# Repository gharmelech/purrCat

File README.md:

# **purrCat**

This is a novelty PCB Art of a purring cat.

Feel free to use this project or parts of it at will, but please give credit when doing so.

While this is an open source project, I am selling kits and assembled units for 10 and 15 USD respectivly.  
Please consider supporting us by [ordering here](https://forms.gle/wS7aRQJ3xb9KGsVB8).

## **Art**
The art was made by Taly Reznik - [@trollworks](https://www.instagram.com/trollworks/?fbclid=IwAR2XS3pt9mpKQIKOb-wqeVHk0iGZXp5bulvpvjSy-UH8qeWS0hPnVhlgy5U)  
Go check out her awesome work!

## **Hardware Description**
The project is based on TI's msp430fr2111 MCU. The current software could fit in (and easily compiled for) msp430fr2110 and could probably be further optimized to fit msp430fr2100, but going with the 2111 model leaves a lot of room for future expansion with just a small price difference.  

Purring is achived with a round radial vibration motor, which is low-side controlled with an nmos transistor.  
In addition, the eyes light up using reverse-mounted LEDs (might be worthwhile to change it to a side view LED in the future).  

Petting is detected using capacitive touch.  
There are 4 touch pads on the PCB, but only 1 is in use in the current FW.

### **Some FW details**

#### **Picky Cat!**
I wanted to make the cat as realistic as possible, so it only likes petting between 0.5 and 2Hz.  
(*Since I'm not doing swipe detection, it would also work with tapping. I might change it in a future version*)  
This is achived using a 2s sample buffer with 125ms slots. if the pad is touched for more than 3 slots in a row, the buffer zeroes.  
Furthermore, purring only starts after at least 1s of petting.

#### **Realistic Purring**
I have programmed a simple PWM function to make the vibration feel like real purring.  
It has dynamic change to the duty cycle, this creates the subtle ramp-up and ramp-down typical of a cat's purring.  
I tried a sinusoidal PWM function, but it didn't have the right feel to it.

#### **Programming and flashing**
The MCU is programmed using Code Composer Studio IDE.  
For software flashing I use a TI dev board LAUNCHPAD MSP-EXP430FR2433, which is the lowest cost programmer option available, though I assume you could make a flashing device out of an arduino.  
I left 3x2mm pitch pads for programming right near the MCU.  
They are arranged (from top to bottom) GND-SBWTCK-SBWTDIO, an additional connection to VCC is required and could be obtained from the battery clip.

### **Power Consumption**
The FW used to feature a distinct power saving mode, but changing the wait timer to RTC with VLO clock source randered that mode as unnedded.  
It is still available in code using a #define flag.

In the current configuration, sampling consumes about 2 micro Ampere - around 60uW at nominal 3V.  
When Purring, i.e. when the motor and the LEDs are enabled, the current consumption is about 22mA - 66mW at nonminal 3V.

The final design uses a cr2032 lithium cell which are rated at about 240mAh.  
While theoretical battery life should have been roughly 8 hours of purring or about 6 years of idle,  
The 240mAh rating is given at much lower current draw than that of the active purring.  
At 20mA, most cr2032 have a capacity of a mere 10-15mAh, giving only about 30 minutes of active purring.

I don't have a good explantion for it, but idle time also seems to substencialy lower than the theoretical - getting to around one week.

Note that this is not linear and even a small reduction in current draw while purring would result in longer operation time.  
Sadly, I was'nt able to find a way to reduce to consumption enough.

#### **LiPo mod**
Giving the poor battery life, I designed a small PCB holding an LDO and a charge connector for a LiPo, to be soldered instead of the battery clip.
The thought of using a LiPo crossed my mind several times, but I deemed it unvaiabel because of cost and required PCB space for a charge controller.
Finally, I had the realization to use a generic LiPo charger externaly (which could be obtained from AliExpress for very cheap) instead of making it onboard.
I did changed the current select resistor on the charger such that the max charge current will be 100 mA - suitable for the tiny LiPo I use.

I decided to use a 501015 60mAh battery.
Because these are rated at 1C, we get a runtime much closer to the theoretical value - about 1.5 hours of purring!
I have used a sub-optimal LDO with 30 uA quiescent current, which becomes the dominant current draw during idle.
I calculated arround 40 days of idle time, but have not ran this long time test yet.

### **Parts List**
- MCU: msp430fr2111
- LED: 2x 0805 LED (reverse mounted, color of your choice)
- Capacitors: 2x0805 10uF MLCC (1 for the MCU and 1 for the Motor), 1x0603 100nF MLCC (for the MCU)
- Resistors: 3x0603 1k Ohm (current limiting for the transistor and the LEDs), 1x0603 100k Ohm (pulldown for the transistor, could be omitted as the driver pin is push-pull)
- Diode: 1x0603 schottky diode (I used Kyocera AVX SD0603S040S0R2)
- Transistor: 1xSOT3 NMOS Transistor (I used Nexperia NXV55UNR)
- Battery clip: 1x Keystone 3034 (cr2032 battery holder), note that not all battery holders can fit in the PCBs footprint)
- Vibration motor: 1x 10mm round radial vibration motor(or smaller), note that there are no pads for soldering it. one lead should be connected to vcc(I used the cap for it) and the other to the transistor drain pin (I made a bigger pad to accomodate this).

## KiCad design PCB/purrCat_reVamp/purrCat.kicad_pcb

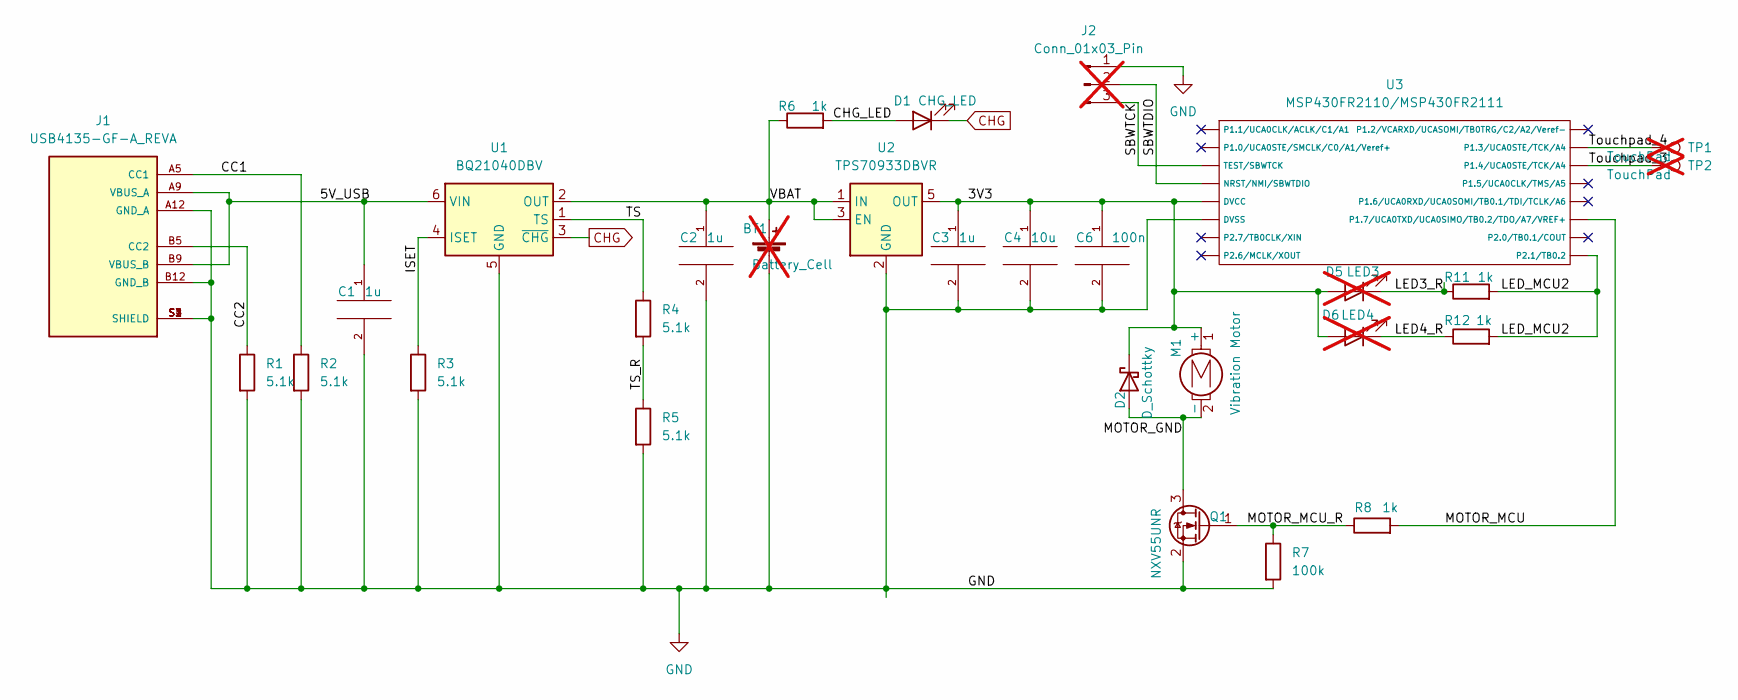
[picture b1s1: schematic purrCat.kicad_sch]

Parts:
BT1: Battery_Cell; bat_solder_pads; not fitted
C1, C2, C3: 1u; C_0603_1608Metric
C4: 10u; C_0805_2012Metric
C6: 100n; C_0402_1005Metric
D1: CHG_LED; LED_0603_1608Metric
D2: D_Schottky; D_0603_1608Metric
D5: LED3; LED_1206_3216Metric_shinethrough; not fitted
D6: LED4; LED_1206_3216Metric_shinethrough; not fitted
J1: USB4135-GF-A_REVA; USB_C_Receptacle_GCT_USB4135-GF-A_6P_TopMnt_Horizontal; PARTREV A
J2: Conn_01x03_Pin; PinHeader_1x03_programmer; not fitted
M1: Vibration Motor; vibration_motor
Q1: NXV55UNR; SOT-23
R1, R2, R3, R4, R5: 5.1k; R_0603_1608Metric
R6, R8, R11, R12: 1k; R_0603_1608Metric
R7: 100k; R_0603_1608Metric
TP1, TP2: TouchPad; touchPad; not fitted
U1: BQ21040DBV; SOT-23-6
U2: TPS70933DBVR; SOT-23-5
U3: MSP430FR2110/MSP430FR2111; TSSOP-16_4.4x5mm_P0.65mm

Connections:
/3V3: C3.1, C4.1, C6.1, D2.1 (K), D5.2 (A), D6.2 (A), M1.1 (+), U2.5 (OUT), U3.5 (DVCC)
/5V_USB: C1.1, J1.A9 (VBUS_A), J1.B9 (VBUS_B), U1.6 (VIN)
/CC1: J1.A5 (CC1), R2.1
/CC2: J1.B5 (CC2), R1.1
/CHG_LED: D1.2 (A), R6.2
/ISET: R3.1, U1.4 (ISET)
/LED3_R: D5.1 (K), R11.1
/LED4_R: D6.1 (K), R12.1
/LED_MCU2: R11.2, R12.2, U3.9 (P2.1/TB0.2)
/MOTOR_GND: D2.2 (A), M1.2 (-), Q1.3 (D)
/MOTOR_MCU: R8.2, U3.11 (P1.7/UCA0TXD/UCA0SIMO/TB0.2/TDO/A7/VREF+)
/MOTOR_MCU_R: Q1.1 (G), R7.1, R8.1
/SBWTCK: J2.3, U3.3 (TEST/SBWTCK)
/SBWTDIO: J2.2, U3.4 (NRST/NMI/SBWTDIO)
/TS: R4.1, U1.1 (TS)
/TS_R: R4.2, R5.1
/Touchpad_3: TP2.1, U3.14 (P1.4/UCA0STE/TCK/A4)
/Touchpad_4: TP1.1, U3.15 (P1.3/UCA0STE/TCK/A4)
/VBAT: BT1.1 (+), C2.1, R6.1, U1.2 (OUT), U2.1 (IN), U2.3 (EN)
CHG: D1.1 (K), U1.3 (~CHG)
GND: BT1.2 (-), C1.2, C2.2, C3.2, C4.2, C6.2, J1.A12 (GND_A), J1.B12 (GND_B), J1.S1 (SHIELD), J1.S2 (SHIELD), J1.S3 (SHIELD), J1.S4 (SHIELD), J2.1, Q1.2 (S), R1.2, R2.2, R3.2, R5.2, R7.2, U1.5 (GND), U2.2 (GND), U3.6 (DVSS)

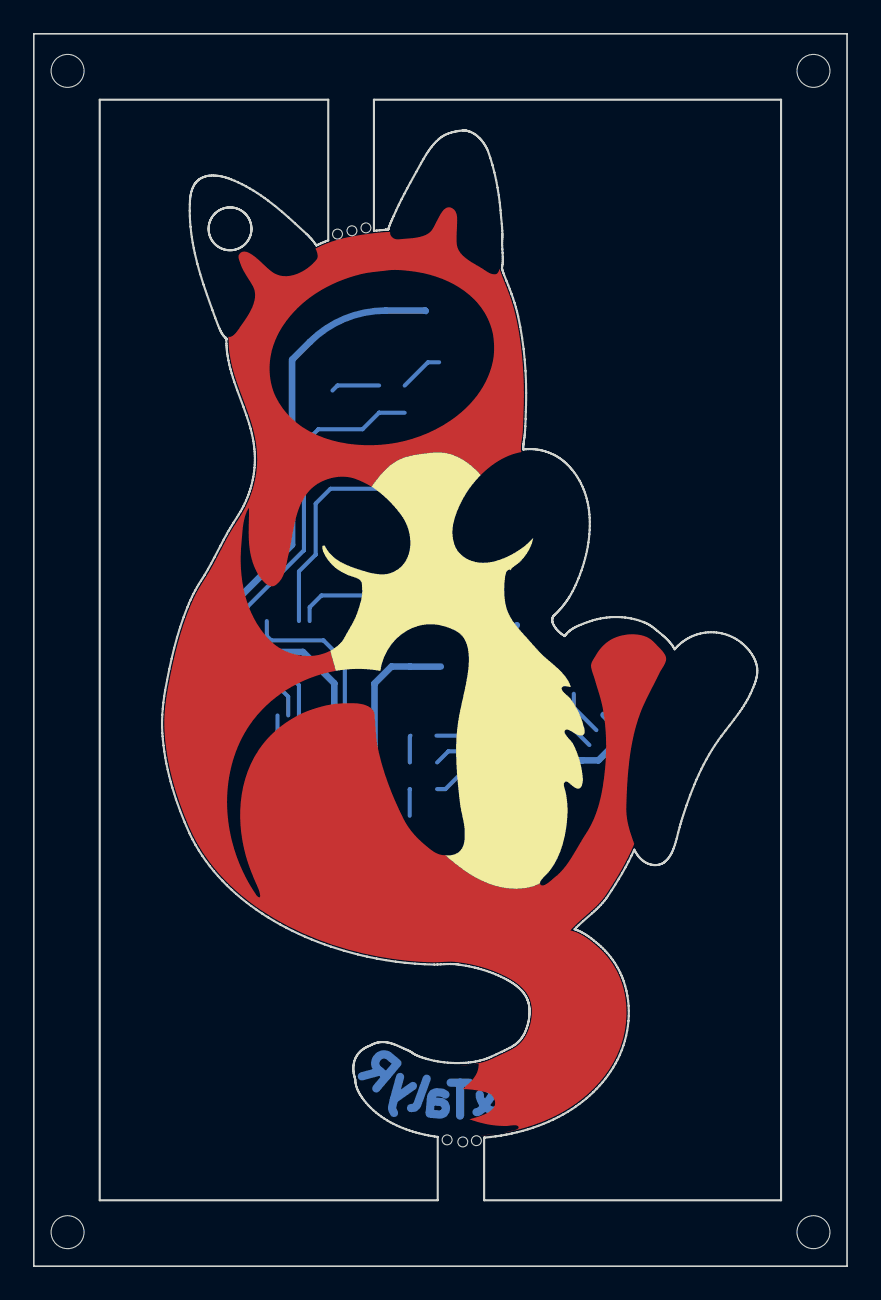
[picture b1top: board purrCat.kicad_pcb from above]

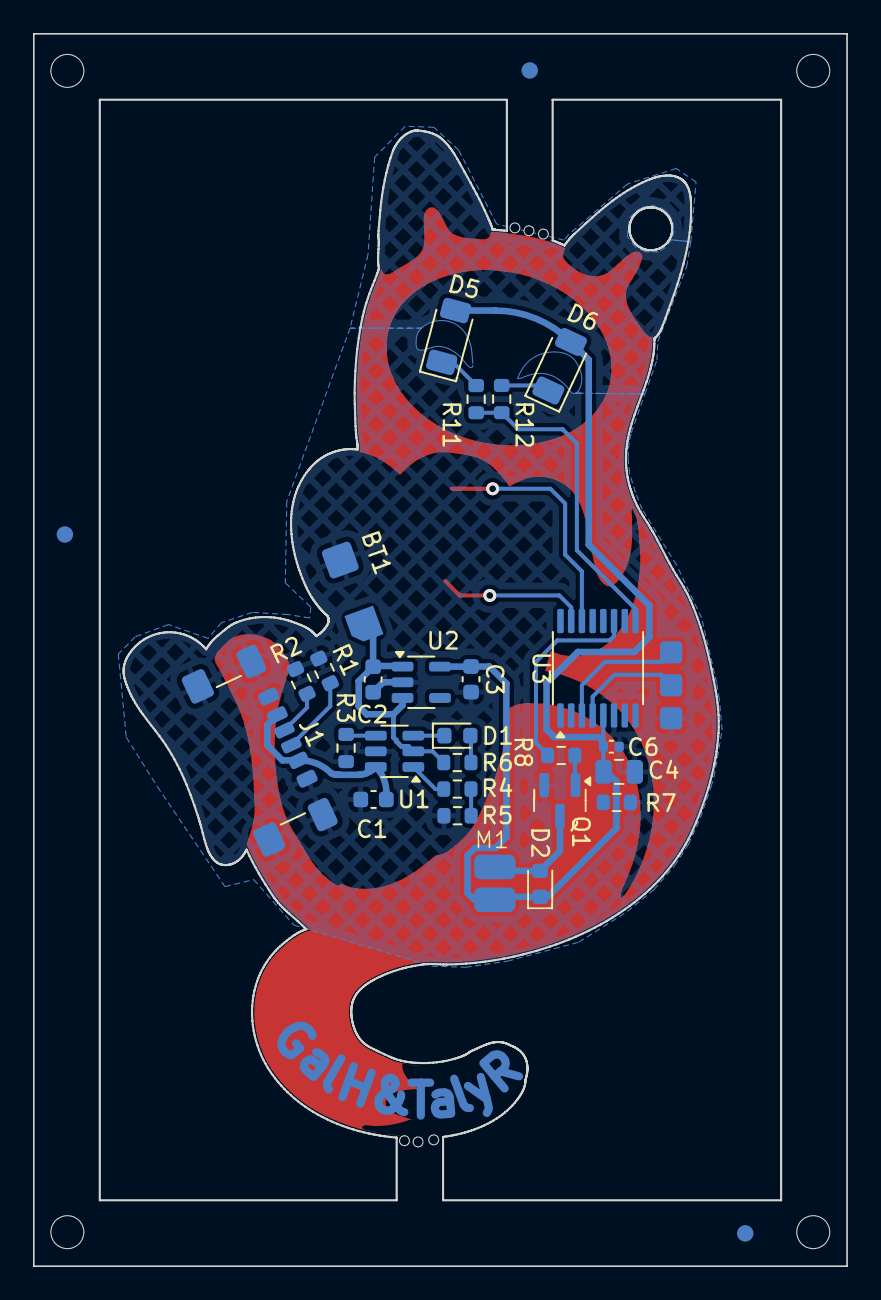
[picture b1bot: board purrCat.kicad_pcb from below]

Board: 2 copper layers, 49.3 x 74.7 mm, 29 parts (27 on the bottom side), 21 nets.

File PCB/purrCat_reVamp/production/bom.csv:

Designator,Footprint,Quantity,Value,LCSC Part #
"C1, C2, C3",0603,3,1u,
C4,0805,1,10u,
C6,0402,1,100n,
D1,0603,1,CHG_LED,
D2,0603,1,D_Schottky,
J1,USB_C_Receptacle_GCT_USB4135-GF-A_6P_TopMnt_Horizontal,1,USB4135-GF-A_REVA,
M1,vibration_motor,1,Vibration Motor,
Q1,SOT-23,1,NXV55UNR,
"R1, R2, R3, R4, R5",0603,5,5.1k,
"R11, R12, R6, R8",0603,4,1k,
R7,0603,1,100k,
U1,SOT-23-6,1,BQ21040DBV,
U2,SOT-23-5,1,TPS70933DBVR,
U3,TSSOP-16_4.4x5mm_P0.65mm,1,MSP430FR2110/MSP430FR2111,

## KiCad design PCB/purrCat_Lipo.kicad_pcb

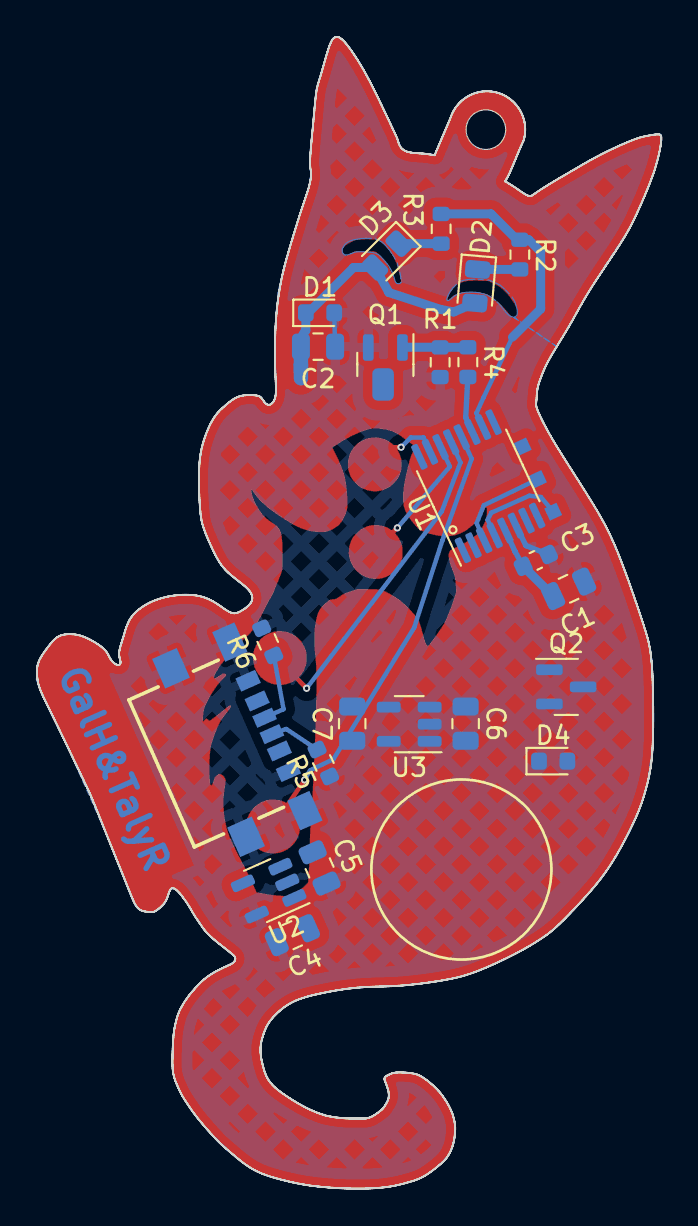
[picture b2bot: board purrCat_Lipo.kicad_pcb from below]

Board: 2 copper layers, 34.7 x 64.0 mm, 24 parts (23 on the bottom side), 12 nets.

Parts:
C1, C2: 10u; C_0805_2012Metric
C3: 100n; C_0603_1608Metric
C4, C5, C6, C7: 1u; C_0805_2012Metric
D1, D4: D_Schottky; D_0603_1608Metric
D2, D3: LED; LED_0805_2012Metric
J1: USB4135-GF-A_REVA; GCT_USB4135-GF-A_REVA
Q1: Q_NMOS_GSD; SOT-23
Q2: Q_PMOS_GSD; SOT-23
R1: 100k; R_0603_1608Metric
R2, R3, R4: 1k; R_0603_1608Metric
R5, R6: 5.1k; R_0603_1608Metric
Ref**: Val**; biggerCat_kicad_layers
U1: MSP430FR2110/MSP430FR2111; TSSOP-16_4.4x5mm_P0.65mm
U2: MCP73811T-420I-OT; SOT-23-5
U3: TPS7A0533PDBV; SOT-23-5

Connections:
/3V3: C1.1, C2.1, C3.1, C7.1, D1.1 (K), D2.2 (A), D3.2 (A), U1.5 (DVCC), U3.5 (OUT)
/5V_USB: C4.1, D4.2 (A), J1.A9 (VBUS_A), J1.B9 (VBUS_B), Q2.1 (G), U2.1 (CEN), U2.4 (VDD)
/CC1: J1.A5 (CC1), R6.1
/CC2: J1.B5 (CC2), R5.1
/LED1_R: D2.1 (K), R2.1
/LED2_R: D3.1 (K), R3.1
/LED_MCU: R2.2, R3.2, U1.10 (P2.0/TB0.1/COUT)
/MOTOR_MCU: R4.2, U1.11 (P1.7/UCA0TXD/UCA0SIMO/TB0.2/TDO/A7/VREF+)
/MOTOR_MCU_R: Q1.1 (G), R1.1, R4.1
/VBAT: C5.1, Q2.2 (S), U2.3 (VBAT)
/VIN: C6.1, D4.1 (K), Q2.3 (D), U3.1 (IN), U3.3 (EN)
GND: C1.2, C2.2, C3.2, C4.2, C5.2, C6.2, C7.2, D1.2 (A), J1.A12 (GND_A), J1.B12 (GND_B), J1.S1 (SHIELD), J1.S2 (SHIELD), J1.S3 (SHIELD), J1.S4 (SHIELD), Q1.2 (S), R1.2, R5.2, R6.2, U1.6 (DVSS), U2.2 (VSS), U2.5 (PROG), U3.2 (GND)

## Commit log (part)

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2022-07-01 Initial Files upload
    Includes the CCS project for the software and folder structure for rest of the project
2022-07-02 Led turn on with purr
2022-09-23 idle power optimization
2022-09-27 Firmware version 1
    Firmware in working condition.
    one touch pad, eyes light up when purring
    ~1 micro amp ideal mode
    ~20 micro amp working mode
    ~20 mili amp purring mode
2022-09-27 PCB files upload
    PCB files and schematics along with library for the unique footprints
2022-09-27 Art Upload
    Original art and svg with layers for footprint creation
2022-10-09 Battery life test bench
2022-10-09 Fix typos
2022-10-13 sample power optimization
    Change wait between samples to use RTC with VLO rather than watchdog --> resulted in ~2uA power consumption.
    Reduced sample power consumption renders the idle mode redundant, so it is disabled using a parameter
2023-03-21 change sampling slot size, documentation, switch magic numbers to define
2023-03-21 change time base for wait calculation and clean code
2024-07-19 Change to msp430fr2110
    + minor spell changes in beautifying
2024-07-19 new design!
    +all sort of junk kicad files - will cleanup later
2024-07-19 art upload
2024-07-20 some layout work - will probably change
2024-07-22 more pcb work
2024-07-29 pcb done with mouse-bite frame
2024-07-30 update BOM and fix some DNP and footprints
2024-10-12 many changes😅
